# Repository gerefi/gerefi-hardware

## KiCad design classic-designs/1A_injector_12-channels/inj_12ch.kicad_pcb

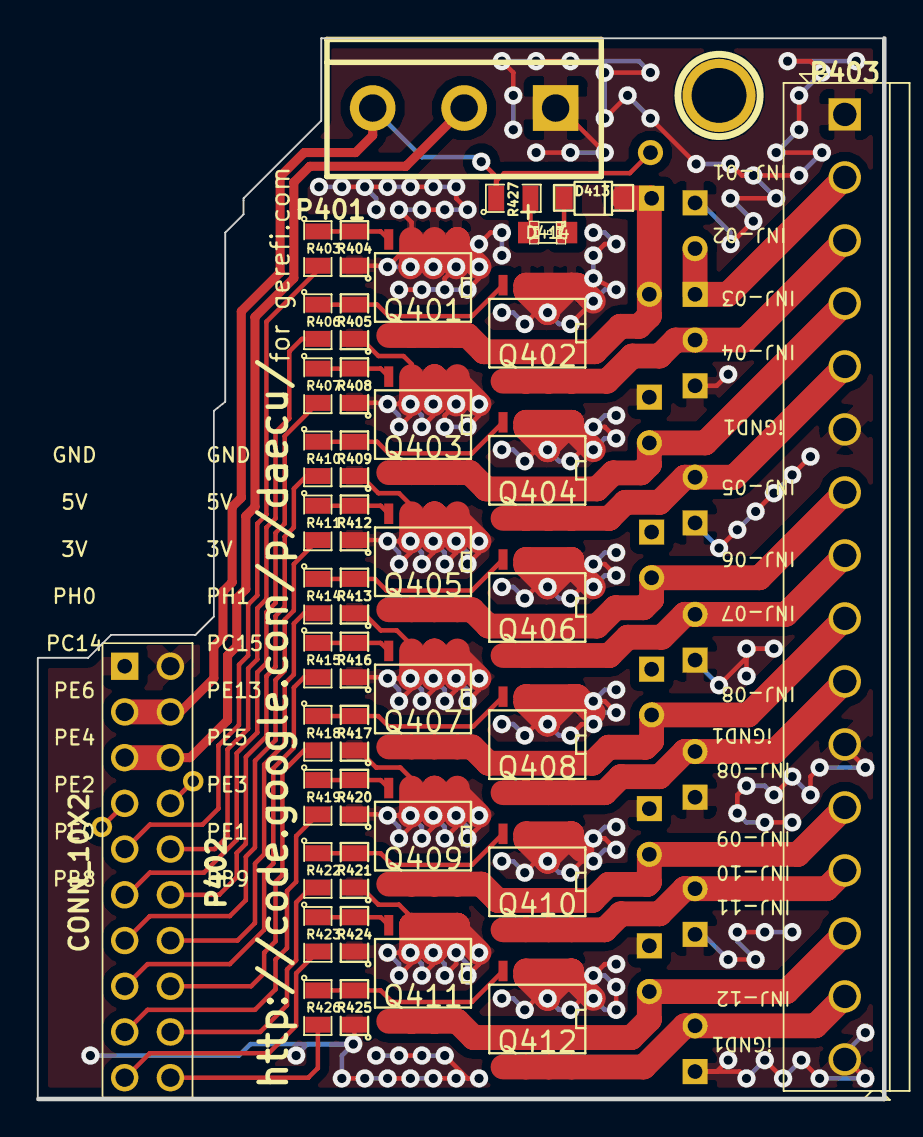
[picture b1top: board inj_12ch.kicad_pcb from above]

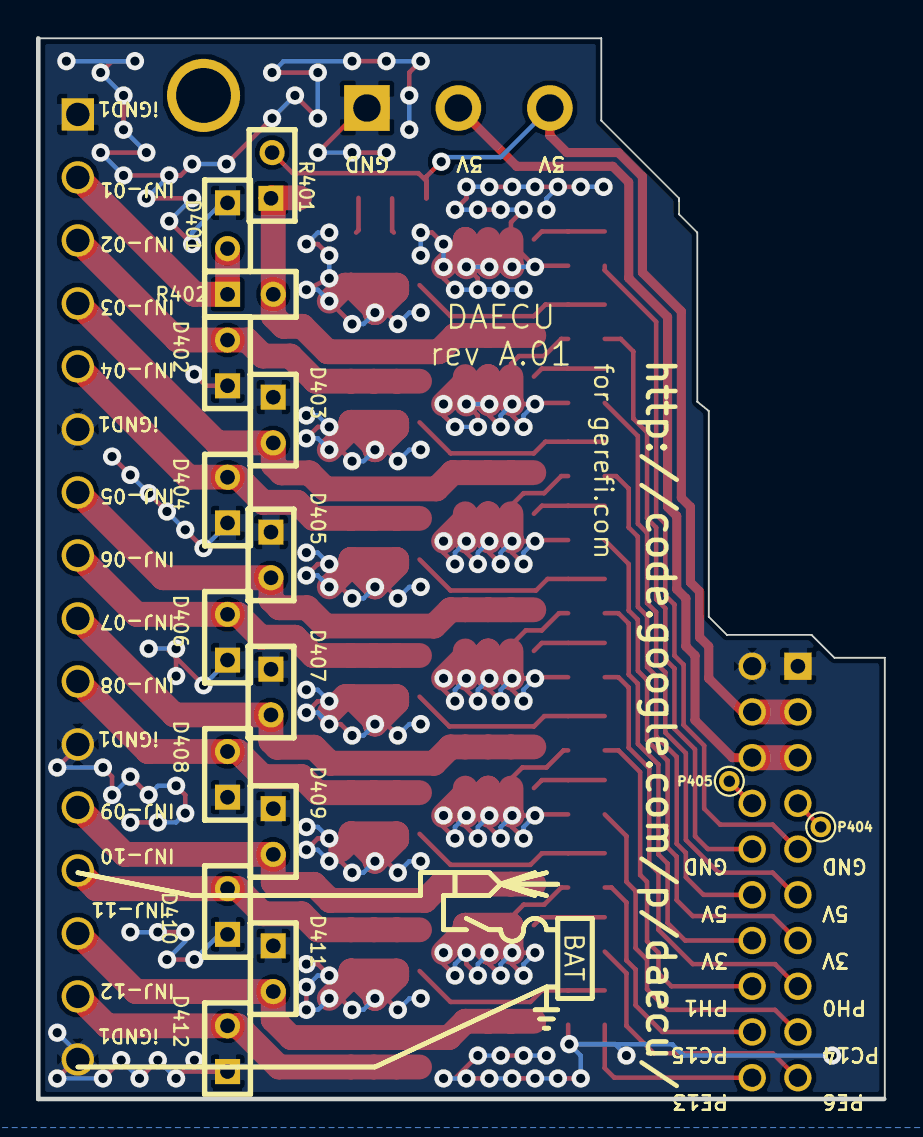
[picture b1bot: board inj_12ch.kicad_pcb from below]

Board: 2 copper layers, 47.0 x 58.9 mm, 59 parts (16 on the bottom side), 44 nets.

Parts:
D401, D402, D403, D404, D405, D406, D407, D408, D409, D410, D411, D412: DIODE; SIL-2
D413: DIODE; SOD-123
D414: LED_0805; LED-0805_A
M401: CONN_1; 1pin
P401: CONN_3; bornier3
P402: CONN_10X2; PIN_ARRAY_10X2_M
P403: CONN_16; SIL-16_3.5MM
P404, P405: CONN_1; PINTST
Q401, Q402, Q403, Q404, Q405, Q406, Q407, Q408, Q409, Q410, Q411, Q412: OVP_DRIVER; SO8E_ST
R401: OPT; SIL-2
R402: 0R; SIL-2
R403, R406, R407, R410, R411, R414, R415, R418, R419, R422, R423, R426: 20R; SM0805
R404, R405, R408, R409, R412, R413, R416, R417, R420, R421, R424, R425, R427: 1K; SM0805

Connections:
/3.3V: P401.2, P402.5, P402.6
/5V: P401.3, P402.3, P402.4, R401.2, R427.1
/INJ-01: D413.2, Q401.2, R401.1, R402.2
/INJ-01_2: D401.2, P403.2, R402.1
/INJ-01_5V: P402.9, R403.2
/INJ-02: D402.2, P403.3, Q402.2
/INJ-02_5V: P402.10, R406.2
/INJ-03: D403.2, P403.4, Q403.2
/INJ-03_5V: P402.11, R407.2
/INJ-04: D404.2, P403.5, Q404.2
/INJ-04_5V: P402.12, R410.2
/INJ-05: D405.2, P403.7, Q405.2
/INJ-05_5V: P402.13, R411.2
/INJ-06: D406.2, P403.8, Q406.2
/INJ-06_5V: P402.14, R414.2
/INJ-07: D407.2, P403.9, Q407.2
/INJ-07_5V: P402.15, R415.2
/INJ-08: D408.2, P403.10, Q408.2
/INJ-08_5V: P402.16, R418.2
/INJ-09: D409.2, P403.12, Q409.2
/INJ-09_5V: P402.17, R419.2
/INJ-10: D410.2, P403.13, Q410.2
/INJ-10_5V: P402.18, R422.2
/INJ-11: D411.2, P403.14, Q411.2
/INJ-11_5V: P402.19, R423.2
/INJ-12: D412.2, P403.15, Q412.2
/INJ-12_5V: P402.20, R426.2
/PH0: P402.7, P404.1
/PH1: P402.8, P405.1
GND: D401.1, D402.1, D403.1, D404.1, D405.1, D406.1, D407.1, D408.1, D409.1, D410.1, D411.1, D412.1, P401.1, P402.1, P402.2, P403.1, P403.6, P403.11, P403.16, Q401.3, Q402.3, Q403.3, Q404.3, Q405.3, Q406.3, Q407.3, Q408.3, Q409.3, Q410.3, Q411.3, Q412.3, R404.1, R405.1, R408.1, R409.1, R412.1, R413.1, R416.1, R417.1, R420.1, R421.1, R424.1, R425.1
unnamed: Q410.1, R421.2, R422.1
unnamed: Q408.1, R417.2, R418.1
unnamed: Q412.1, R425.2, R426.1
unnamed: D413.1, D414.2
unnamed: D414.1, R427.2
unnamed: Q404.1, R409.2, R410.1
unnamed: Q406.1, R413.2, R414.1
unnamed: Q402.1, R405.2, R406.1
unnamed: Q401.1, R403.1, R404.2
unnamed: Q405.1, R411.1, R412.2
unnamed: Q403.1, R407.1, R408.2
unnamed: Q409.1, R419.1, R420.2
unnamed: Q407.1, R415.1, R416.2
unnamed: Q411.1, R423.1, R424.2

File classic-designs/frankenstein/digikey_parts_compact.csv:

### this file was generated by gerefi bom_builder on Sat Feb 22 11:01:39 CST 2014
### 292 components in 2047 lines of frankenstein.cmp
### 65 kinds of components in input file
### 9 entries in BOM dictionary bom_dictionary_digikey.csv
### 2 entries in ignore list
### no BOM record for 1pin_CONN_1
### no BOM record for LED-0805_GREEN
### no BOM record for LED-0805_LED
### no BOM record for LED-0805_RED
### no BOM record for LED-1206_LED
### no BOM record for MICRO-SDCARD-CONNECTOR-3300060P1_MICRO-SDCARD-CONNECTOR-3300060P1
### no BOM record for OSTVN06A150_CONN_6
### no BOM record for PIN_ARRAY-6X1_CONN_6
### no BOM record for PIN_ARRAY_10X2_CONN_10X2
### no BOM record for PIN_ARRAY_10X2_M_CONN_10X2
### no BOM record for PIN_ARRAY_1_CONN_1
### no BOM record for PIN_ARRAY_2X1_CONN_2
### no BOM record for PIN_ARRAY_2_A_CONN_2
### no BOM record for PIN_ARRAY_2_A_JUMPER
### no BOM record for PIN_ARRAY_3X1_CONN_3
### no BOM record for PIN_ARRAY_3_A_CONN_3
### no BOM record for PIN_ARRAY_4x1_CONN_4
### no BOM record for PIN_ARRAY_5x2_CONN_5X2
### no BOM record for SIL-16_3.5MM_CONN_16
### no BOM record for SIL-2_0R
### no BOM record for SIL-2_CONN_2
### no BOM record for SIL-2_DIODE
### no BOM record for SIL-2_JUMPER
### no BOM record for SIL-2_OPT
### no BOM record for SIL-2_TEST
### no BOM record for SM0805_.1uF
### no BOM record for SM0805_0.01uF
### no BOM record for SM0805_0.1uF
### no BOM record for SM0805_100
### no BOM record for SM0805_1000pF
### no BOM record for SM0805_10K
### no BOM record for SM0805_10k
### no BOM record for SM0805_10uF
### no BOM record for SM0805_120
### no BOM record for SM0805_1500
### no BOM record for SM0805_1K
### no BOM record for SM0805_1M
### no BOM record for SM0805_1uF
### no BOM record for SM0805_20K
### no BOM record for SM0805_2700
### no BOM record for SM0805_4.7uF
### no BOM record for SM0805_4700pF
### no BOM record for SM0805_47pF
### no BOM record for SM0805_500K
### no BOM record for SM0805_5k
### no BOM record for SM0805_LED
### no BOM record for SM1206_LED
### no BOM record for SOD-123_DIODE
### no BOM record for bornier3_CONN_3
### no BOM record for pin_array_10x2_CONN_10X2
### no BOM record for pin_array_3x2_CONN_3X2
### no BOM record for pin_array_4x2_CONN_4X2
### no BOM record for sot23_DOUBLE_SCHOTTKY
### no BOM record for uMAX-uSOP_10_MAX9939




1,670-1190-1-ND,mini USB socket
4,P1.0KACT-ND,some reference
12,P20.0CCT-ND,driver current limiting
1,296-11654-1-ND,CAN driver
12,497-11082-1-ND,12A low-side MOSFET
1,MAX9926UAEE+TCT-ND,VR chip
3,TC4427AVOA-ND,1.5A dual driver
3,497-4943-1-ND,quad op-amp
1,768-1007-1-ND,USB TTL chip

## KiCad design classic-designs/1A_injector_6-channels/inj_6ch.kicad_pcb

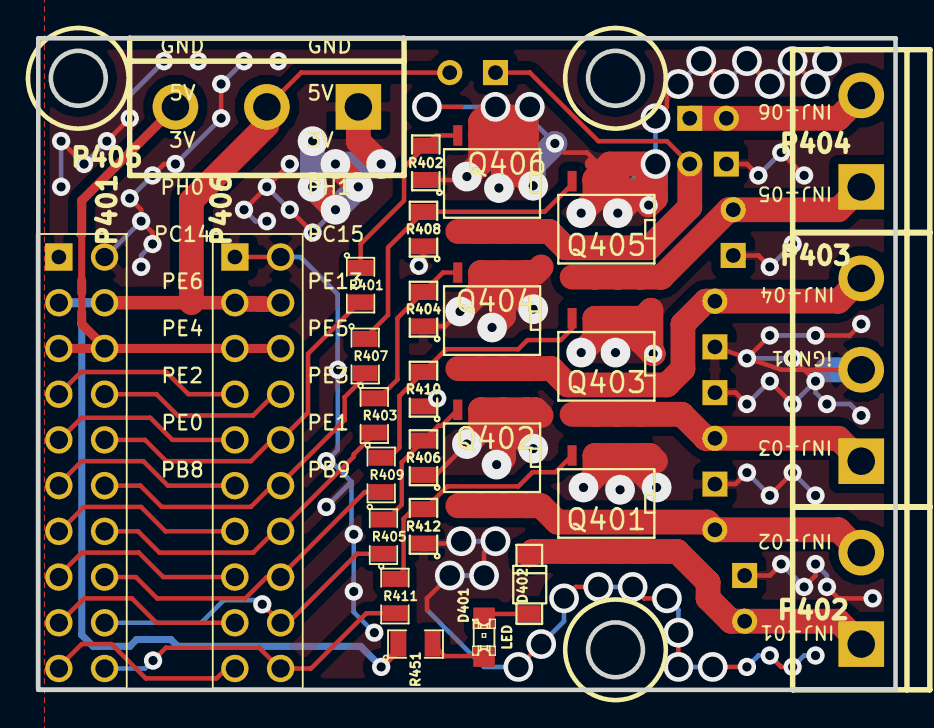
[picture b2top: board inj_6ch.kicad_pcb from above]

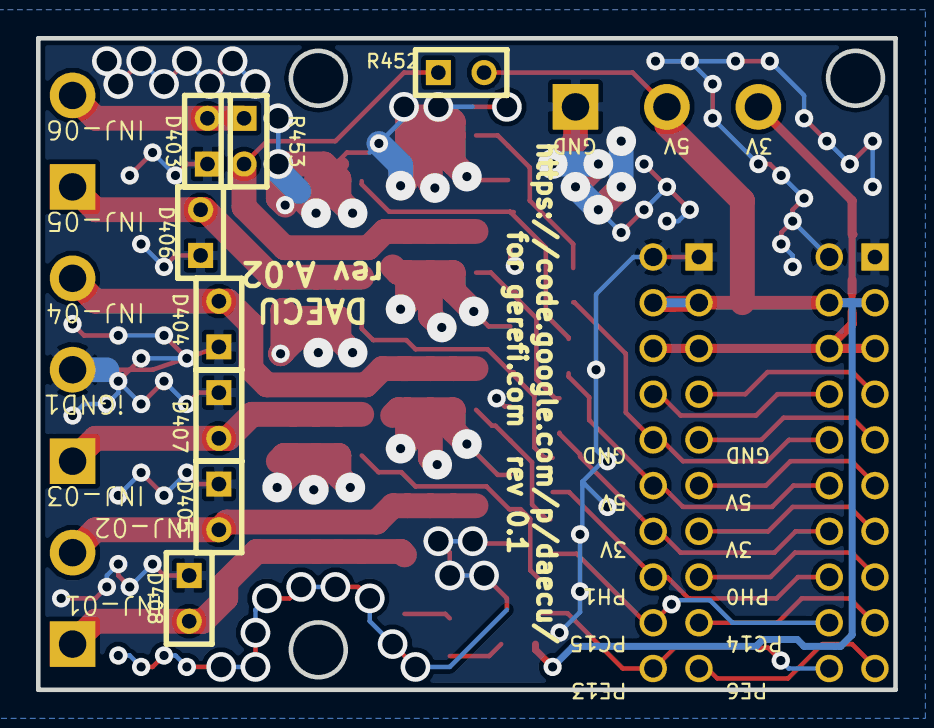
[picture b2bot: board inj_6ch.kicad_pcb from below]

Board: 2 copper layers, 47.6 x 36.2 mm, 35 parts (8 on the bottom side), 32 nets.

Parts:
D401: LED; LED-0805
D402: DIODE; SOD-123
D403, D404, D405, D406, D407, D408: DIODE; SIL-2
P401, P406: HEADER_10X2; pin_array_10x2
P402, P404: CONN_2; bornier2
P403, P405: CONN_3; bornier3
Q401, Q402, Q403, Q404, Q405, Q406: OVP_DRIVER; SO8E_ST
R401, R403, R405, R407, R409, R411: 20R; SM0805
R402, R404, R406, R408, R410, R412, R451: 1K; SM0805
R452: OPT; SIL-2
R453: 0R; SIL-2

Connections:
/3.3V: P401.5, P401.6, P405.3, P406.5, P406.6
/5V: P401.3, P401.4, P405.2, P406.3, P406.4, R451.1, R452.2
/INJ-01: D402.2, D408.2, P402.1, Q401.2
/INJ-01_5V: P401.20, P406.20, R411.2
/INJ-02: D405.2, P402.2, Q402.2
/INJ-02_5V: P401.18, P406.18, R405.2
/INJ-03: D407.2, P403.1, Q403.2
/INJ-03_5V: P401.16, P406.16, R409.2
/INJ-04: D404.2, P403.3, Q404.2
/INJ-04_5V: P401.14, P406.14, R403.2
/INJ-05: D406.2, P404.1, Q405.2
/INJ-05_5V: P401.12, P406.12, R407.2
/INJ-06: Q406.2, R452.1, R453.2
/INJ-06_2: D403.2, P404.2, R453.1
/INJ-06_5V: P401.10, P406.10, R401.2
/PB8: P401.19, P406.19
/PC14: P401.9, P406.9
/PE0: P401.17, P406.17
/PE2: P401.15, P406.15
/PE4: P401.13, P406.13
/PE6: P401.11, P406.11
/PH0: P401.7, P406.7
/PH1: P401.8, P406.8
GND: D403.1, D404.1, D405.1, D406.1, D407.1, D408.1, P401.1, P401.2, P403.2, P405.1, P406.1, P406.2, Q401.3, Q402.3, Q403.3, Q404.3, Q405.3, Q406.3, R402.1, R404.1, R406.1, R408.1, R410.1, R412.1
unnamed: D401.1, R451.2
unnamed: D401.2, D402.1
unnamed: Q406.1, R401.1, R402.2
unnamed: Q404.1, R403.1, R404.2
unnamed: Q403.1, R409.1, R410.2
unnamed: Q402.1, R405.1, R406.2
unnamed: Q401.1, R411.1, R412.2
unnamed: Q405.1, R407.1, R408.2

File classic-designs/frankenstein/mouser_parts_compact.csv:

### this file was generated by gerefi bom_builder on Sat Mar 08 11:58:11 CST 2014
### 292 components in 2047 lines of frankenstein.cmp
### 65 kinds of components in input file
### 5 entries in BOM dictionary bom_dictionary_mouser.csv
### 0 entries in ignore list
### no BOM record for 1pin_CONN_1
### no BOM record for LED-0805_GREEN
### no BOM record for LED-0805_LED
### no BOM record for LED-0805_RED
### no BOM record for LED-1206_LED
### no BOM record for LOGO_F_LOGO
### no BOM record for LOGO_LOGO
### no BOM record for MICRO-SDCARD-CONNECTOR-3300060P1_MICRO-SDCARD-CONNECTOR-3300060P1
### no BOM record for OSTVN06A150_CONN_6
### no BOM record for PIN_ARRAY-6X1_CONN_6
### no BOM record for PIN_ARRAY_10X2_CONN_10X2
### no BOM record for PIN_ARRAY_10X2_M_CONN_10X2
### no BOM record for PIN_ARRAY_1_CONN_1
### no BOM record for PIN_ARRAY_2X1_CONN_2
### no BOM record for PIN_ARRAY_2_A_CONN_2
### no BOM record for PIN_ARRAY_2_A_JUMPER
### no BOM record for PIN_ARRAY_3X1_CONN_3
### no BOM record for PIN_ARRAY_3_A_CONN_3
### no BOM record for PIN_ARRAY_4x1_CONN_4
### no BOM record for PIN_ARRAY_5x2_CONN_5X2
### no BOM record for SIL-16_3.5MM_CONN_16
### no BOM record for SIL-2_0R
### no BOM record for SIL-2_CONN_2
### no BOM record for SIL-2_DIODE
### no BOM record for SIL-2_JUMPER
### no BOM record for SIL-2_OPT
### no BOM record for SIL-2_TEST
### no BOM record for SM0805_.1uF
### no BOM record for SM0805_0.01uF
### no BOM record for SM0805_0.1uF
### no BOM record for SM0805_100
### no BOM record for SM0805_1000pF
### no BOM record for SM0805_10K
### no BOM record for SM0805_10k
### no BOM record for SM0805_10uF
### no BOM record for SM0805_120
### no BOM record for SM0805_1500
### no BOM record for SM0805_1K
### no BOM record for SM0805_1M
### no BOM record for SM0805_1k
### no BOM record for SM0805_1uF
### no BOM record for SM0805_20K
### no BOM record for SM0805_20R
### no BOM record for SM0805_2700
### no BOM record for SM0805_4.7uF
### no BOM record for SM0805_4700pF
### no BOM record for SM0805_47pF
### no BOM record for SM0805_500K
### no BOM record for SM0805_5k
### no BOM record for SM0805_LED
### no BOM record for SM1206_LED
### no BOM record for SO8E_ST_OVP_DRIVER
### no BOM record for SOD-123_DIODE
### no BOM record for bornier3_CONN_3
### no BOM record for msoic-8_TC4427AVOA
### no BOM record for pin_array_10x2_CONN_10X2
### no BOM record for pin_array_3x2_CONN_3X2
### no BOM record for pin_array_4x2_CONN_4X2
### no BOM record for sot23_DOUBLE_SCHOTTKY
### no BOM record for uMAX-uSOP_10_MAX9939




1,656-DX2R005HN2E700,mini USB socket
1,296-11654-1-ND,CAN driver
1,700-MAX9926UAEE,VR chip
3,595-LMV324IDR,quad op-amp
1,895-FT232RL,USB TTL chip

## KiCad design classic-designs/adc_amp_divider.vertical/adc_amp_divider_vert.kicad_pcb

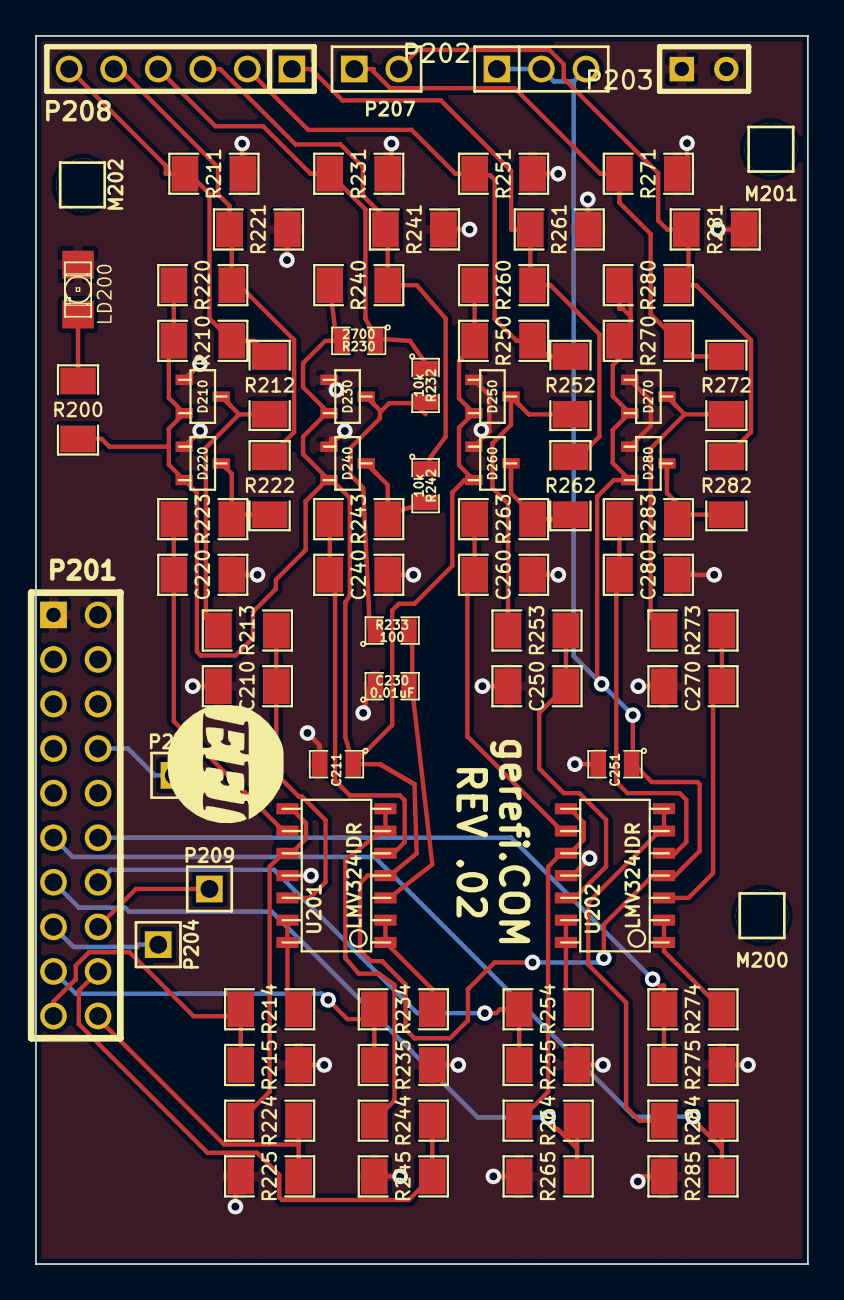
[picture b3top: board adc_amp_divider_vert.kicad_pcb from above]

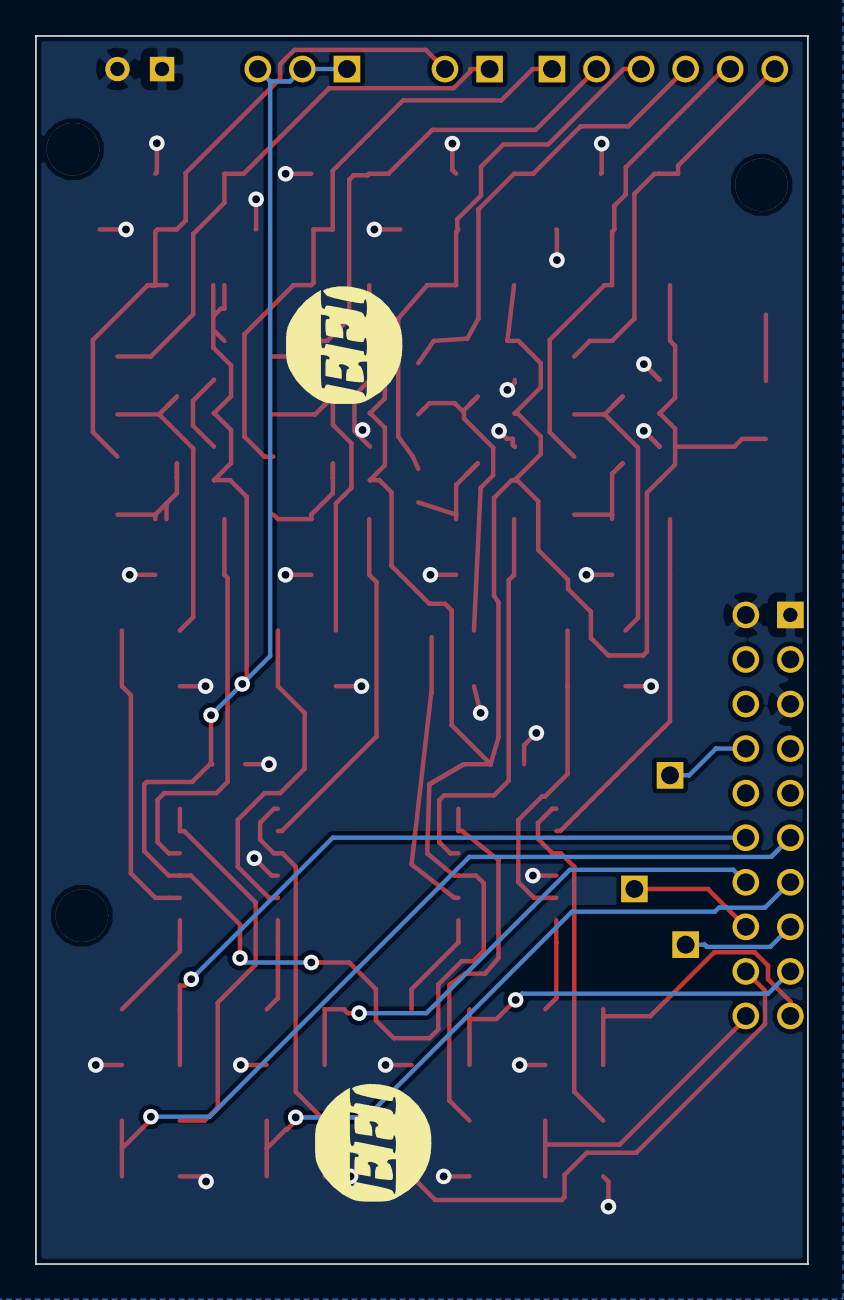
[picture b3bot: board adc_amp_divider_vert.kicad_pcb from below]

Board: 2 copper layers, 44.0 x 70.0 mm, 84 parts (2 on the bottom side), 46 nets.

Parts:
C210, C220, C240, C250, C260, C270, C280: 0.01uF; SM1206
C211, C251: 0.1uF; SM0805
C230: 0.01uF; SM0805
D210, D220, D230, D240, D250, D260, D270, D280: DOUBLE_SCHOTTKY; sot23
G200: LOGO
G201, G202: LOGO; LOGO_F
LD200: LED; LED-1206
M200, M201, M202: CONN_1; PIN_ARRAY_1
P201: CONN_10X2; PIN_ARRAY_10X2
P202: CONN_3; PIN_ARRAY_3X1
P203: CONN_2; SIL-2
P204, P205, P209: CONN_1; PIN_ARRAY_1
P207: CONN_2; PIN_ARRAY_2X1
P208: CONN_6; PIN_ARRAY-6X1
R200, R213, R223, R243, R253, R263, R273, R283: 100; SM1206
R210, R220, R240, R250, R260, R270, R280: 2700; SM1206
R211, R221, R231, R241, R251, R261, R271, R281: 500K; SM1206
R212, R222, R252, R262, R272, R282: 10k; SM1206
R214, R215, R224, R225, R234, R235, R244, R245, R254, R255, R264, R265, R274, R275, R284, R285: 1500; SM1206
R230: 2700; SM0805
R232, R242: 10k; SM0805
R233: 100; SM0805
U201, U202: LMV324IDR; so-14

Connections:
/5V: C211.1, C251.1, D210.3, D220.3, D230.3, D240.3, D250.3, D260.3, D270.3, D280.3, P202.1, P202.2, P202.3, R200.1, R210.2, R220.2, R230.2, R240.2, R250.2, R260.2, R270.2, R280.2, U201.4, U202.4
/INP1: P208.6, R210.1, R211.1, R212.1
/INP2: P208.5, R220.1, R221.1, R222.1
/INP3: P208.4, R230.1, R231.1, R232.1
/INP4: P208.3, R240.1, R241.1, R242.1
/INP5: P208.2, R250.1, R251.1, R252.1
/INP6: P208.1, R260.1, R261.1, R262.1
/INP7: P207.1, R270.1, R271.1, R272.1
/INP8: P207.2, R280.1, R281.1, R282.1
/OUT1: P201.19, R214.2, R215.1
/OUT2: P201.20, R224.2, R225.1
/OUT3: P201.17, R234.2, R235.1
/OUT4: P201.18, R244.2, R245.1
/OUT5: P201.14, R254.2, R255.1
/OUT6: P201.13, R264.2, R265.1
/OUT7: P201.12, R274.2, R275.1
/OUT8: P201.11, R284.2, R285.1
/PA4: P201.16, P209.1
/PA5: P201.15, P204.1
/PC0: P201.8, P205.1
GND: C210.1, C211.2, C220.1, C230.1, C240.1, C250.1, C251.2, C260.1, C270.1, C280.1, D210.1, D220.1, D230.1, D240.1, D250.1, D260.1, D270.1, D280.1, LD200.1, P201.1, P201.2, P201.5, P203.1, P203.2, R211.2, R215.2, R221.2, R225.2, R231.2, R235.2, R241.2, R245.2, R251.2, R255.2, R261.2, R265.2, R271.2, R275.2, R281.2, R285.2, U201.11, U202.11
unnamed: D240.2, R242.2, R243.1
unnamed: D220.2, R222.2, R223.1
unnamed: D250.2, R252.2, R253.1
unnamed: D260.2, R262.2, R263.1
unnamed: D210.2, R212.2, R213.1
unnamed: C280.2, R283.2, U202.5
unnamed: C270.2, R273.2, U202.3
unnamed: R284.1, U202.6, U202.7
unnamed: R274.1, U202.1, U202.2
unnamed: C240.2, R243.2, U201.5
unnamed: LD200.2, R200.2
unnamed: C260.2, R263.2, U202.9
unnamed: C250.2, R253.2, U202.12
unnamed: R264.1, U202.8, U202.10
unnamed: R254.1, U202.13, U202.14
unnamed: D270.2, R272.2, R273.1
unnamed: D280.2, R282.2, R283.1
unnamed: R244.1, U201.6, U201.7
unnamed: R234.1, U201.1, U201.2
unnamed: R224.1, U201.8, U201.10
unnamed: C220.2, R223.2, U201.9
unnamed: C210.2, R213.2, U201.12
unnamed: C230.2, R233.2, U201.3
unnamed: R214.1, U201.13, U201.14
unnamed: D230.2, R232.2, R233.1

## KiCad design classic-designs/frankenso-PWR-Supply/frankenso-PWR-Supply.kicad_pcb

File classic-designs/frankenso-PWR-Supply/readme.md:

https://gerefi.com/forum/viewtopic.php?f=4&t=394

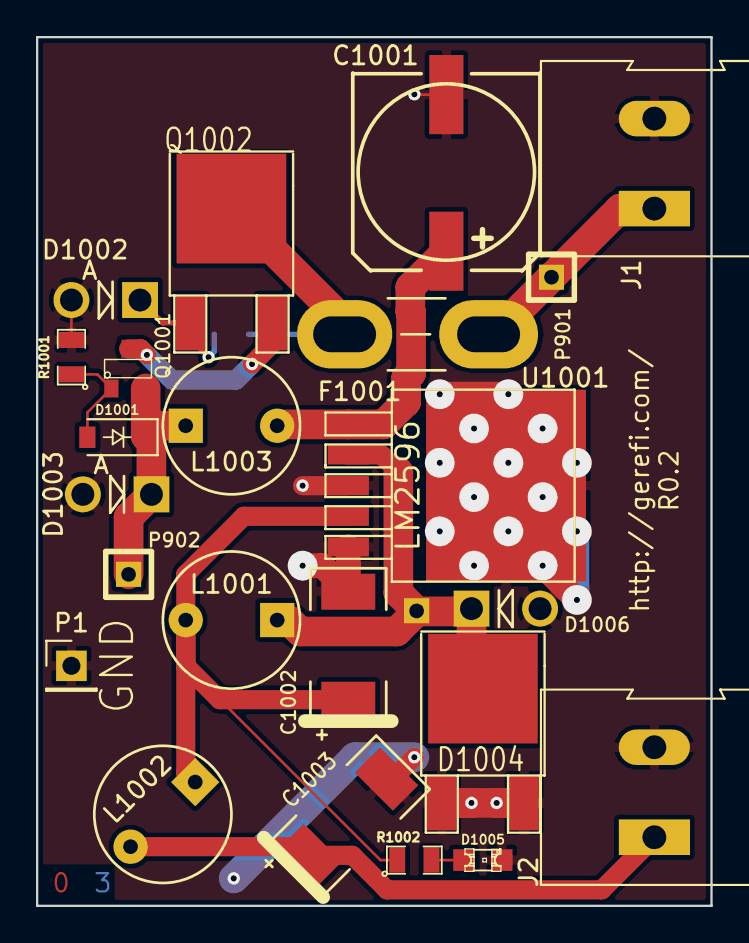
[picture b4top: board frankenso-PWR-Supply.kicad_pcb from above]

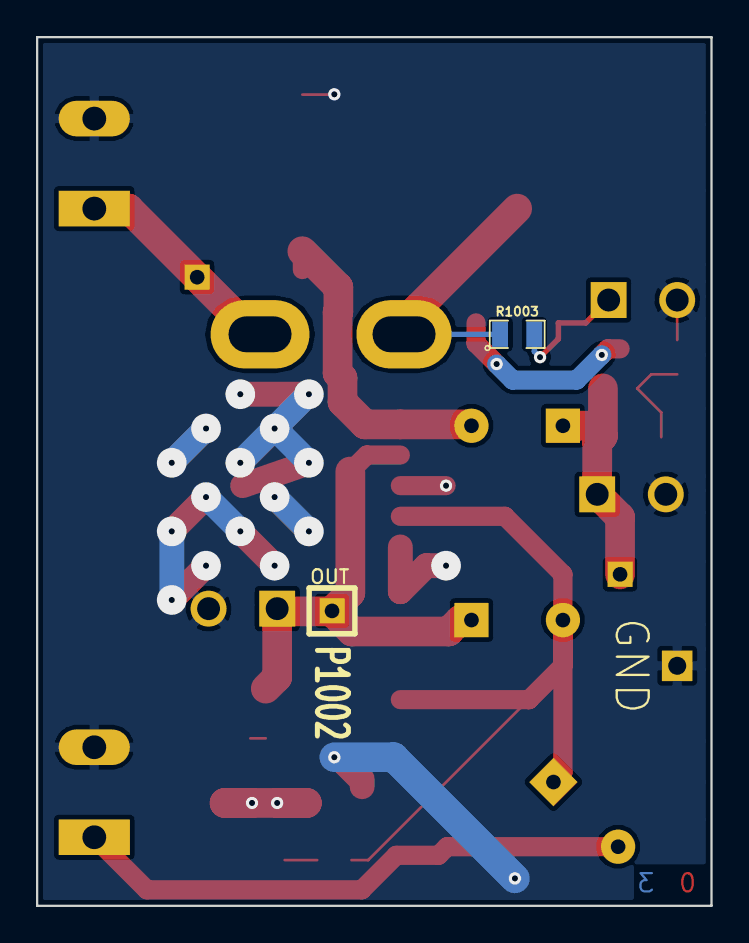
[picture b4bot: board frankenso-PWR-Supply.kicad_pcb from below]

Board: 2 copper layers, 37.5 x 48.3 mm, 25 parts (2 on the bottom side), 12 nets.

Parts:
C1001: 330uF 35V; SMDSVP10
C1002, C1003: 220uF 16V; SM2512
D1001: 7.5V; D_SOD-123
D1002: 17V; Diode_DO-41_SOD81_Vertical_AnodeUp
D1003: 24V; Diode_DO-41_SOD81_Vertical_AnodeUp
D1004: DIODESCH; DPAK2
D1005: LED-grn; LED-0805
D1006: DIODESCH; Diode_DO-41_SOD81_Vertical_AnodeUp
F1001: 1.5A; BladeFuse-Mini
J1, J2: Screw_Terminal_1x02; AK300-2
L1001, L1002, L1003: 68uH; INDUCTOR_V
P1: CONN_1; Pin_Header_Straight_1x01_Pitch2.54mm
P901, P902, P1002: CONN_1; SIL-1
Q1001: 20V; SOT23
Q1002: 200V; DPAK2
R1001: 39k; SM0805
R1002: 1k; SM0805
R1003: 100k; SM0805
U1001: LM2596; DPAK5

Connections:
/5V-REG: C1003.1, J2.1, L1002.2
/FB: C1002.1, L1001.2, L1002.1, R1002.1, U1001.4
/OUT: D1004.2, D1006.1, L1001.1, P1002.1, U1001.2
/VBAT: C1001.1, L1003.2, U1001.1
/Vf: F1001.2, Q1002.2, R1003.1
/Vin: F1001.1, J1.1, P901.1
/Vs1: D1002.1, Q1002.1, R1003.2
/Vs2: Q1001.3, Q1002.3
GND: C1001.2, C1002.2, C1003.2, D1002.2, D1003.2, D1004.1, D1004.3, D1005.2, D1006.2, J1.2, J2.2, P1.1, R1001.2, U1001.3, U1001.5
unnamed: D1001.1, D1003.1, L1003.1, P902.1, Q1001.2
unnamed: D1001.2, Q1001.1, R1001.1
unnamed: D1005.1, R1002.2
